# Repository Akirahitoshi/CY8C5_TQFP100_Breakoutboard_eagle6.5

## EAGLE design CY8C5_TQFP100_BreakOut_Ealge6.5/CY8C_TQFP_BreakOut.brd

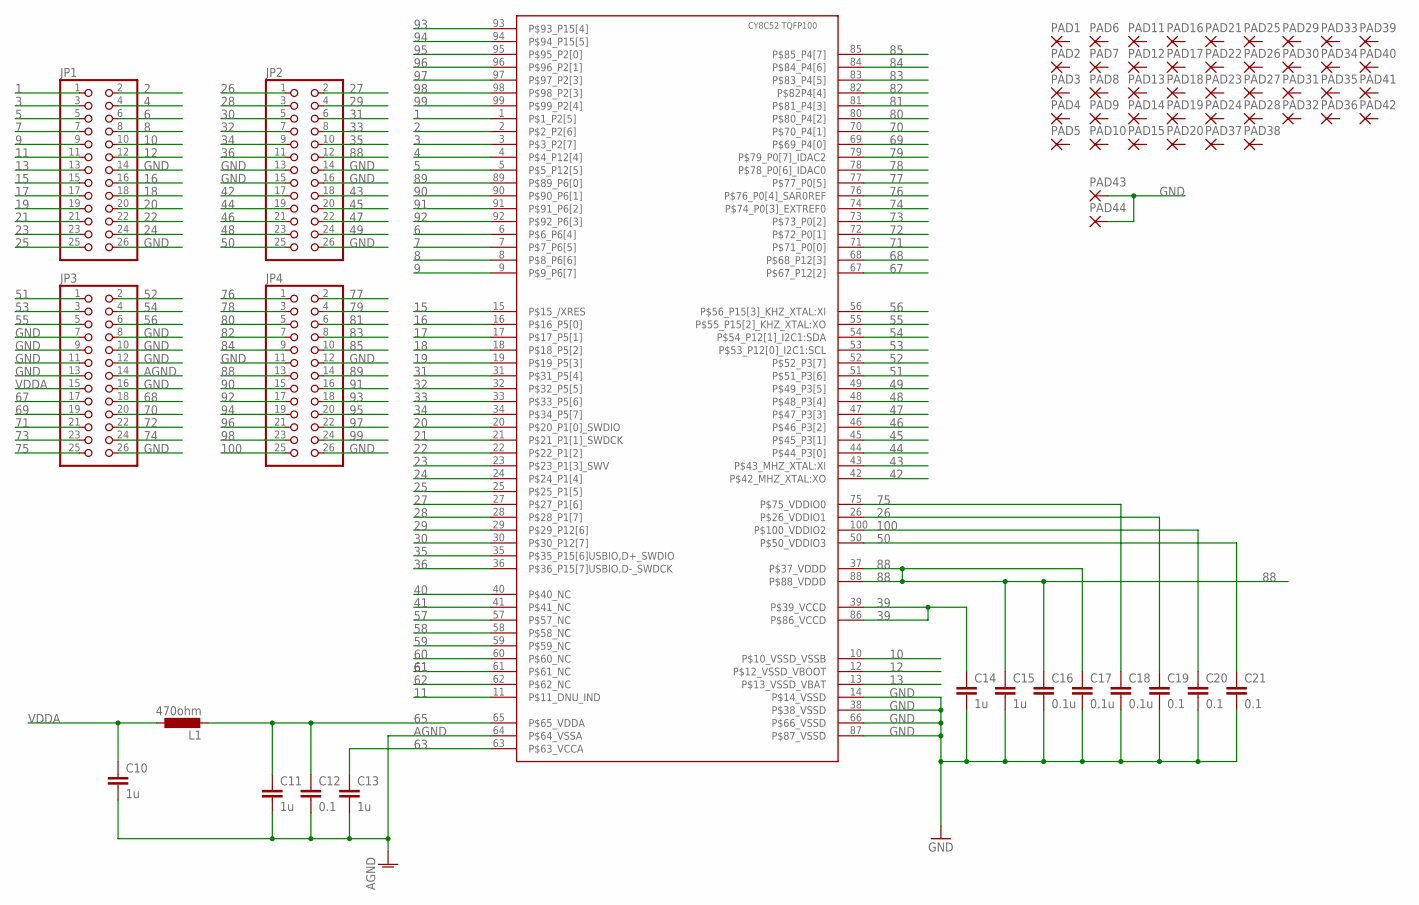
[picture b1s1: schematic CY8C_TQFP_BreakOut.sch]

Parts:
C10, C11, C14, C15: 1u; C3216
C12, C19, C20, C21: 0.1; C2012
C13: 1u; C2012
C16, C17, C18: 0.1u; C2012
IC1: PSOC5LP52XX_TQFP100; TQFP100_MOD
JP1, JP2, JP3, JP4: PINHD-2X13; 2X13
L1: 470ohm; L3225M
PAD1, PAD2, PAD3, PAD4, PAD5, PAD6, PAD7, PAD8, PAD9, PAD10, PAD11, PAD12, PAD13, PAD14, PAD15, PAD16, PAD17, PAD18, PAD19, PAD20, PAD21, PAD22, PAD23, PAD24, PAD25, PAD26, PAD27, PAD28, PAD29, PAD30, PAD31, PAD32, PAD33, PAD34, PAD35, PAD36, PAD37, PAD38, PAD39, PAD40, PAD41, PAD42, PAD43, PAD44: SMD2; SMD1,27-2,54

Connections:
1: IC1.1 (P$1_P2[5]), JP1.1
2: IC1.2 (P$2_P2[6]), JP1.2
3: IC1.3 (P$3_P2[7]), JP1.3
4: IC1.4 (P$4_P12[4]), JP1.4
5: IC1.5 (P$5_P12[5]), JP1.5
6: IC1.6 (P$6_P6[4]), JP1.6
7: IC1.7 (P$7_P6[5]), JP1.7
8: IC1.8 (P$8_P6[6]), JP1.8
9: IC1.9 (P$9_P6[7]), JP1.9
10: IC1.10 (P$10_VSSD_VSSB), JP1.10
11: IC1.11 (P$11_DNU_IND), JP1.11
12: IC1.12 (P$12_VSSD_VBOOT), JP1.12
13: IC1.13 (P$13_VSSD_VBAT), JP1.13
15: IC1.15 (P$15_/XRES), JP1.15
16: IC1.16 (P$16_P5[0]), JP1.16
17: IC1.17 (P$17_P5[1]), JP1.17
18: IC1.18 (P$18_P5[2]), JP1.18
19: IC1.19 (P$19_P5[3]), JP1.19
20: IC1.20 (P$20_P1[0]_SWDIO), JP1.20
21: IC1.21 (P$21_P1[1]_SWDCK), JP1.21
22: IC1.22 (P$22_P1[2]), JP1.22
23: IC1.23 (P$23_P1[3]_SWV), JP1.23
24: IC1.24 (P$24_P1[4]), JP1.24
25: IC1.25 (P$25_P1[5]), JP1.25
26: C19.1, IC1.26 (P$26_VDDIO1), JP2.1
27: IC1.27 (P$27_P1[6]), JP2.2
28: IC1.28 (P$28_P1[7]), JP2.3
29: IC1.29 (P$29_P12[6]), JP2.4
30: IC1.30 (P$30_P12[7]), JP2.5
31: IC1.31 (P$31_P5[4]), JP2.6
32: IC1.32 (P$32_P5[5]), JP2.7
33: IC1.33 (P$33_P5[6]), JP2.8
34: IC1.34 (P$34_P5[7]), JP2.9
35: IC1.35 (P$35_P15[6]USBIO,D+_SWDIO), JP2.10
36: IC1.36 (P$36_P15[7]USBIO,D-_SWDCK), JP2.11
39: C14.1, IC1.39 (P$39_VCCD), IC1.86 (P$86_VCCD)
40: IC1.40 (P$40_NC)
41: IC1.41 (P$41_NC)
42: IC1.42 (P$42_MHZ_XTAL:XO), JP2.17
43: IC1.43 (P$43_MHZ_XTAL:XI), JP2.18
44: IC1.44 (P$44_P3[0]), JP2.19
45: IC1.45 (P$45_P3[1]), JP2.20
46: IC1.46 (P$46_P3[2]), JP2.21
47: IC1.47 (P$47_P3[3]), JP2.22
48: IC1.48 (P$48_P3[4]), JP2.23
49: IC1.49 (P$49_P3[5]), JP2.24
50: C21.1, IC1.50 (P$50_VDDIO3), JP2.25
51: IC1.51 (P$51_P3[6]), JP3.1
52: IC1.52 (P$52_P3[7]), JP3.2
53: IC1.53 (P$53_P12[0]_I2C1:SCL), JP3.3
54: IC1.54 (P$54_P12[1]_I2C1:SDA), JP3.4
55: IC1.55 (P$55_P15[2]_KHZ_XTAL:XO), JP3.5
56: IC1.56 (P$56_P15[3]_KHZ_XTAL:XI), JP3.6
57: IC1.57 (P$57_NC)
58: IC1.58 (P$58_NC)
59: IC1.59 (P$59_NC)
60: IC1.60 (P$60_NC)
61: IC1.61 (P$61_NC)
62: IC1.62 (P$62_NC)
63: C13.1, IC1.63 (P$63_VCCA)
65: C11.1, C12.1, IC1.65 (P$65_VDDA), L1.2
67: IC1.67 (P$67_P12[2]), JP3.17
68: IC1.68 (P$68_P12[3]), JP3.18
69: IC1.69 (P$69_P4[0]), JP3.19
70: IC1.70 (P$70_P4[1]), JP3.20
71: IC1.71 (P$71_P0[0]), JP3.21
72: IC1.72 (P$72_P0[1]), JP3.22
73: IC1.73 (P$73_P0[2]), JP3.23
74: IC1.74 (P$74_P0[3]_EXTREF0), JP3.24
75: C18.1, IC1.75 (P$75_VDDIO0), JP3.25
76: IC1.76 (P$76_P0[4]_SAR0REF), JP4.1
77: IC1.77 (P$77_P0[5]), JP4.2
78: IC1.78 (P$78_P0[6]_IDAC0), JP4.3
79: IC1.79 (P$79_P0[7]_IDAC2), JP4.4
80: IC1.80 (P$80_P4[2]), JP4.5
81: IC1.81 (P$81_P4[3]), JP4.6
82: IC1.82 (P$82P4[4]), JP4.7
83: IC1.83 (P$83_P4[5]), JP4.8
84: IC1.84 (P$84_P4[6]), JP4.9
85: IC1.85 (P$85_P4[7]), JP4.10
88: C15.1, C16.1, C17.1, IC1.37 (P$37_VDDD), IC1.88 (P$88_VDDD), JP2.12, JP4.13
89: IC1.89 (P$89_P6[0]), JP4.14
90: IC1.90 (P$90_P6[1]), JP4.15
91: IC1.91 (P$91_P6[2]), JP4.16
92: IC1.92 (P$92_P6[3]), JP4.17
93: IC1.93 (P$93_P15[4]), JP4.18
94: IC1.94 (P$94_P15[5]), JP4.19
95: IC1.95 (P$95_P2[0]), JP4.20
96: IC1.96 (P$96_P2[1]), JP4.21
97: IC1.97 (P$97_P2[3]), JP4.22
98: IC1.98 (P$98_P2[3]), JP4.23
99: IC1.99 (P$99_P2[4]), JP4.24
100: C20.1, IC1.100 (P$100_VDDIO2), JP4.25
AGND: C10.2, C11.2, C12.2, C13.2, IC1.64 (P$64_VSSA), JP3.14
GND: C14.2, C15.2, C16.2, C17.2, C18.2, C19.2, C20.2, C21.2, IC1.14 (P$14_VSSD), IC1.38 (P$38_VSSD), IC1.66 (P$66_VSSD), IC1.87 (P$87_VSSD), JP1.14, JP1.26, JP2.13, JP2.14, JP2.15, JP2.16, JP2.26, JP3.7, JP3.8, JP3.9, JP3.10, JP3.11, JP3.12, JP3.13, JP3.16, JP3.26, JP4.11, JP4.12, JP4.26, PAD43.1, PAD44.1
VDDA: C10.1, JP3.15, L1.1

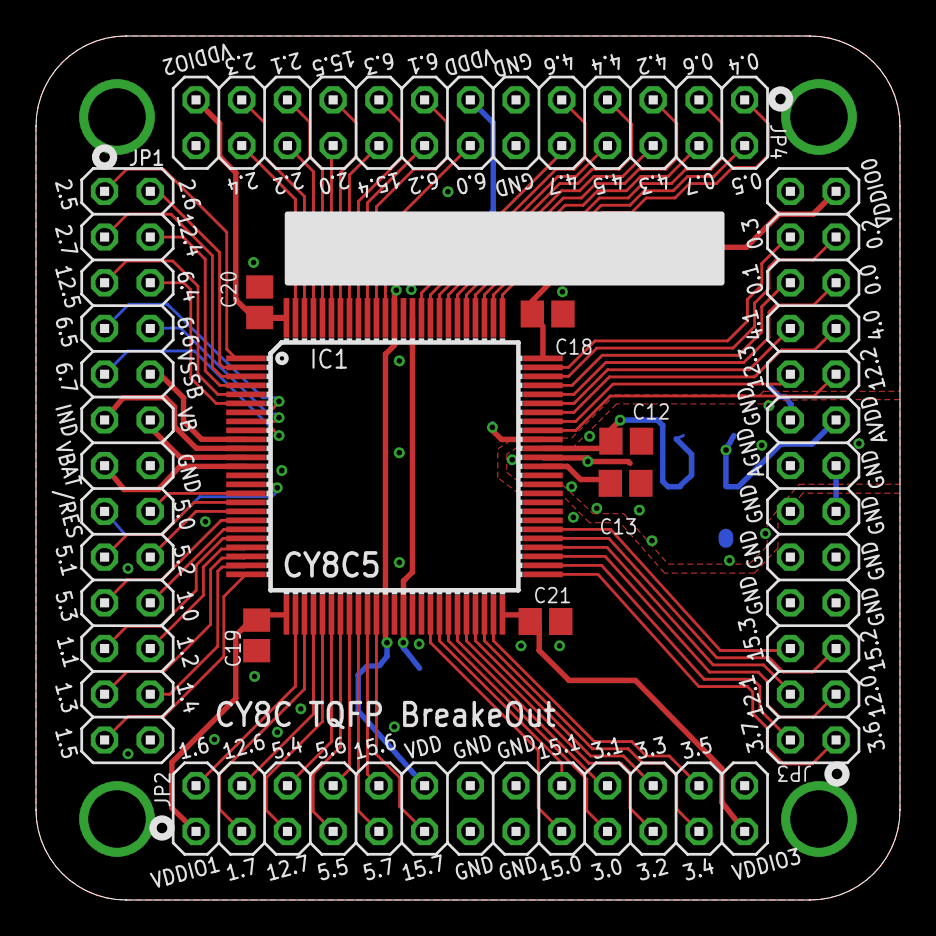
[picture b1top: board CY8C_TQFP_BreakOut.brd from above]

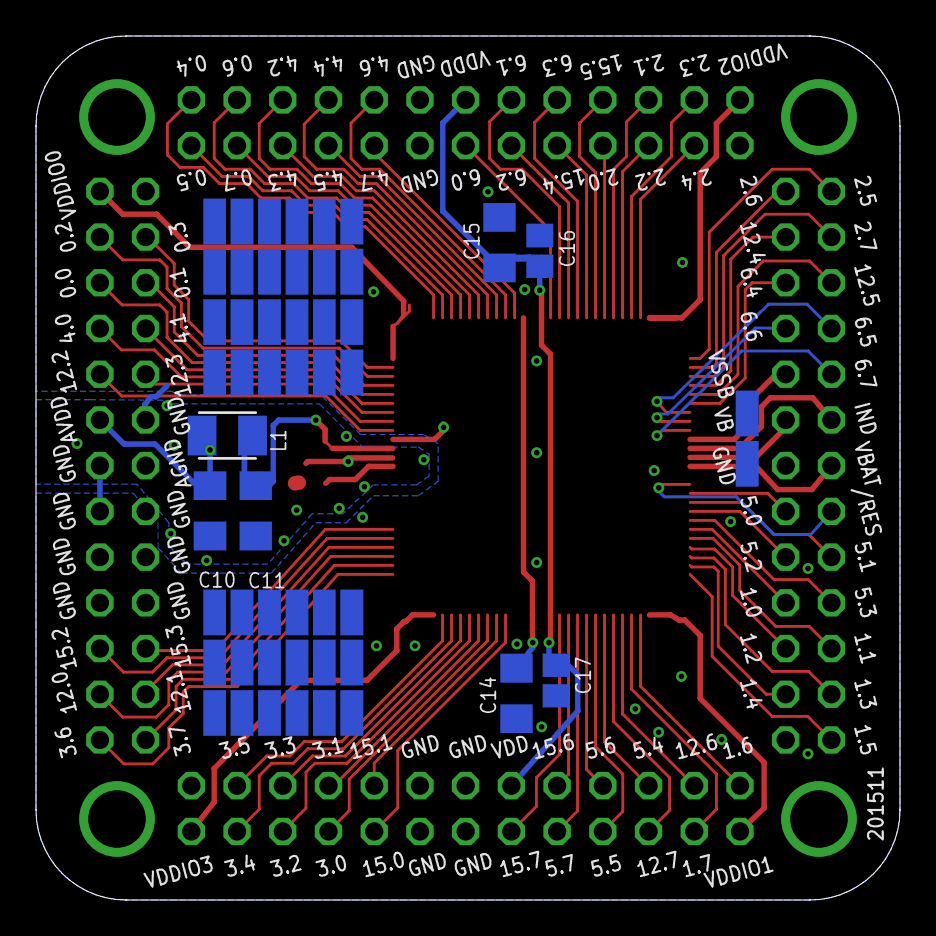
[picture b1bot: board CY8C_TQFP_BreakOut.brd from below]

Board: 2 copper layers, 48.0 x 48.0 mm, 62 parts (51 on the bottom side), 88 nets.

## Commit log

2016-04-12 :circus_tent: Added .gitattributes & .gitignore files
2016-04-12 First commit.
